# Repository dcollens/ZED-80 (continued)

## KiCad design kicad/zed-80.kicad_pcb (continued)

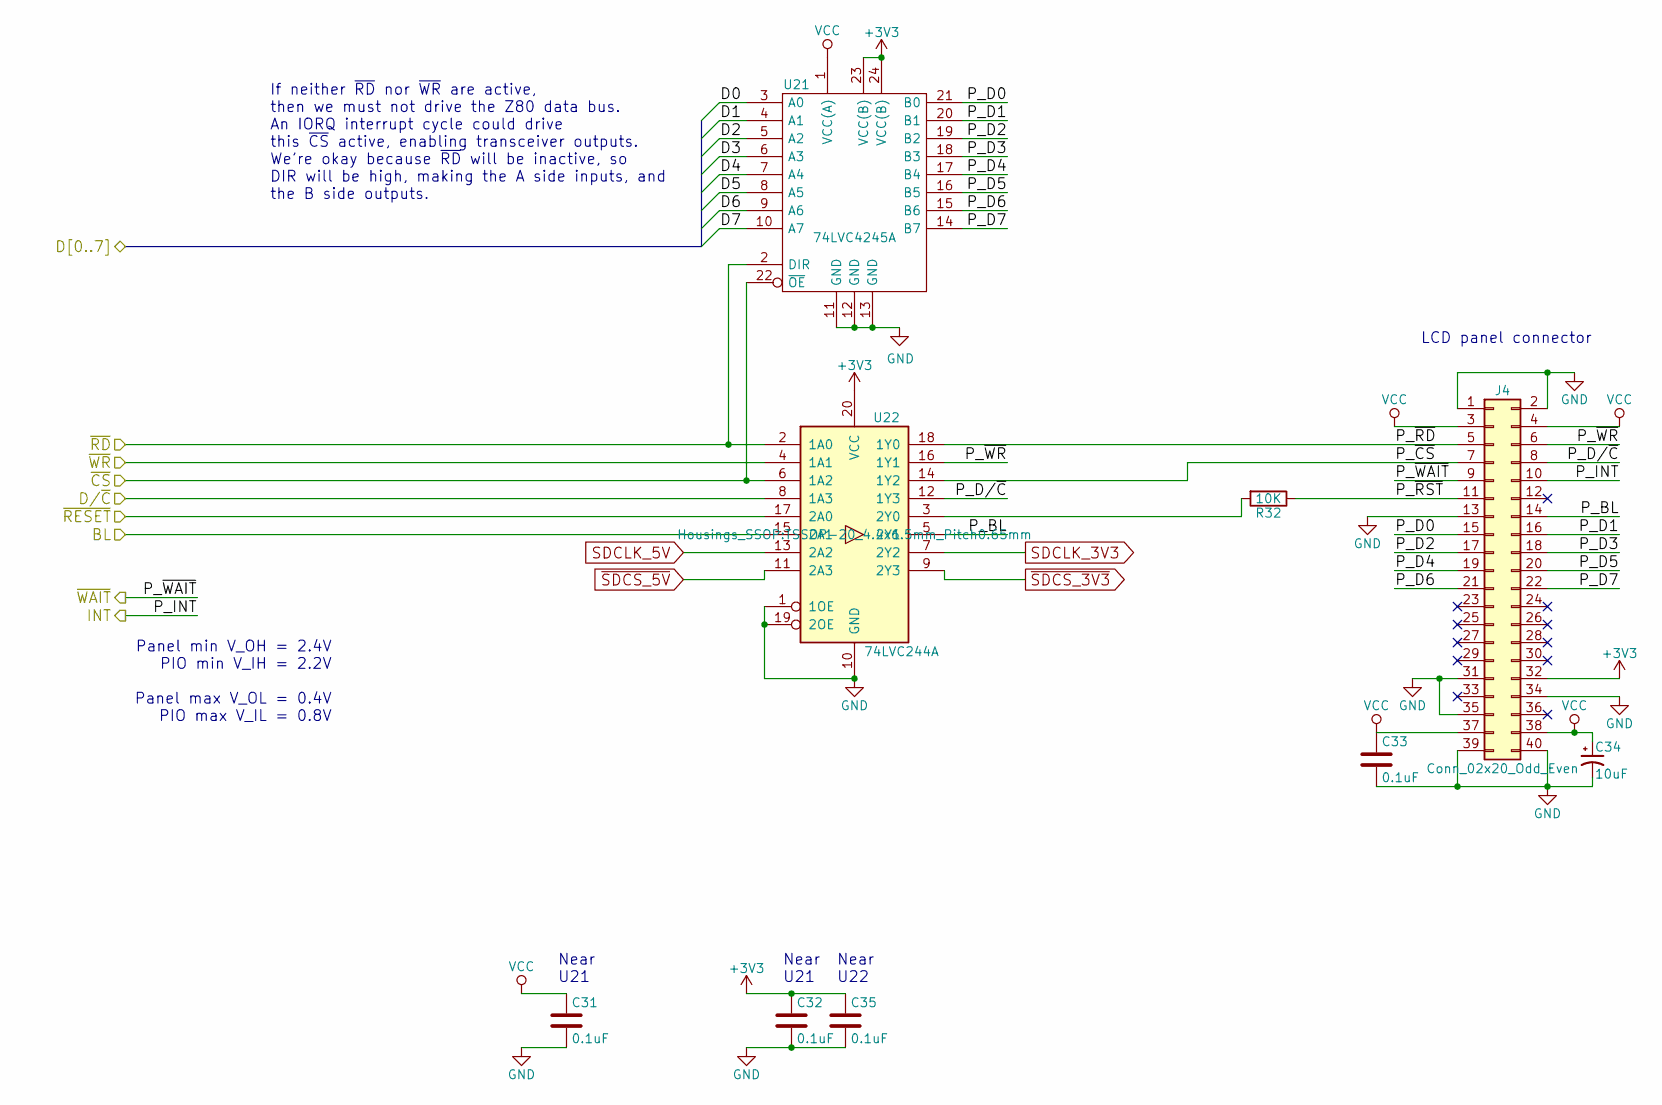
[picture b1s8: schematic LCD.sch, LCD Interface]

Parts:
C31, C32, C33, C35: 0.1uF; C_Disc_D4.3mm_W1.9mm_P5.00mm
C34: 10uF; CP_Radial_D5.0mm_P2.50mm
J4: Conn_02x20_Odd_Even; Pin_Header_Straight_2x20_Pitch2.54mm
R32: 10K; R_0805_HandSoldering
U21: 74LVC4245A; TSSOP-24_4.4x7.8mm_Pitch0.65mm
U22: 74LVC244A; TSSOP-20_4.4x6.5mm_Pitch0.65mm

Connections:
+3V3: C32.1, C35.1, J4.32, U21.23 (VCC(B)), U21.24 (VCC(B)), U22.20 (VCC); also elsewhere on the board
/A0: U22.8 (1A3); also elsewhere on the board
/D0: U21.3 (A0); also elsewhere on the board
/D1: U21.4 (A1); also elsewhere on the board
/D2: U21.5 (A2); also elsewhere on the board
/D3: U21.6 (A3); also elsewhere on the board
/D4: U21.7 (A4); also elsewhere on the board
/D5: U21.8 (A5); also elsewhere on the board
/D6: U21.9 (A6); also elsewhere on the board
/D7: U21.10 (A7); also elsewhere on the board
/LCD/BL: U22.15 (2A1); also elsewhere on the board
/LCD/INT: J4.10; also elsewhere on the board
/LCD/P_BL: J4.14, U22.5 (2Y1)
/LCD/P_D0: J4.15, U21.21 (B0)
/LCD/P_D1: J4.16, U21.20 (B1)
/LCD/P_D2: J4.17, U21.19 (B2)
/LCD/P_D3: J4.18, U21.18 (B3)
/LCD/P_D4: J4.19, U21.17 (B4)
/LCD/P_D5: J4.20, U21.16 (B5)
/LCD/P_D6: J4.21, U21.15 (B6)
/LCD/P_D7: J4.22, U21.14 (B7)
/LCD/P_D/~C: J4.8, U22.12 (1Y3)
/LCD/P_~CS: J4.7, U22.14 (1Y2)
/LCD/P_~RD: J4.5, U22.18 (1Y0)
/LCD/P_~RST: J4.11, R32.1
/LCD/P_~WR: J4.6, U22.16 (1Y1)
/PIO/PIOA7: J4.9; also elsewhere on the board
/~IORQ5: U21.22 (~OE), U22.6 (1A2); also elsewhere on the board
/~RD: U21.2 (DIR), U22.2 (1A0); also elsewhere on the board
/~RESET: U22.17 (2A0); also elsewhere on the board
/~WR: U22.4 (1A1); also elsewhere on the board
GND: C31.2, C32.2, C33.2, C34.2, C35.2, J4.1, J4.2, J4.13, J4.31, J4.34, J4.35, J4.39, J4.40, U21.11 (GND), U21.12 (GND), U21.13 (GND), U22.1 (1OE), U22.10 (GND), U22.19 (2OE); also elsewhere on the board
unnamed: R32.2, U22.3 (2Y0)
SDCLK_3V3: U22.7 (2Y2); also elsewhere on the board
SDCLK_5V: U22.13 (2A2); also elsewhere on the board
VCC: C31.1, C33.1, C34.1, J4.3, J4.4, J4.37, J4.38, U21.1 (VCC(A)); also elsewhere on the board
~SDCS_3V3: U22.9 (2Y3); also elsewhere on the board
~SDCS_5V: U22.11 (2A3); also elsewhere on the board

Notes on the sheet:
LCD panel connector
Near U21
Panel min V_OH = 2.4V PIO min V_IH = 2.2V Panel max V_OL = 0.4V PIO max V_IL = 0.8V
Near U22
If neither ~RD~ nor ~WR~ are active, then we must not drive the Z80 data bus. An IORQ interrupt cycle could drive this ~CS~ active, enabling transceiver outputs. We’re okay because ~RD~ will be inactive, so DIR will be high, making the A side inputs, and the B side outputs.

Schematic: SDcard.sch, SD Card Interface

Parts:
C36, C39, C40: 0.1uF; C_Disc_D4.3mm_W1.9mm_P5.00mm
J7: SD_Card; 101-00405
R33: 50K; R_0805_HandSoldering
R34, R35: 10K; R_0805_HandSoldering
U4: 74AHC32; DIP-14_W7.62mm
U25: 74HCT164; TSSOP-14_4.4x5mm_Pitch0.65mm
U26: 74AHC541; TSSOP-20_4.4x6.5mm_Pitch0.65mm
U27: 74LV165; TSSOP-16_4.4x5mm_Pitch0.65mm

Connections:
+3V3: C36.1, J7.4 (VDD), R33.2, U27.16 (VCC); also elsewhere on the board
/D0: U26.18 (Y0), U27.11 (D0); also elsewhere on the board
/D1: U26.17 (Y1), U27.12 (D1); also elsewhere on the board
/D2: U26.16 (Y2), U27.13 (D2); also elsewhere on the board
/D3: U26.15 (Y3), U27.14 (D3); also elsewhere on the board
/D4: U26.14 (Y4), U27.3 (D4); also elsewhere on the board
/D5: U26.13 (Y5), U27.4 (D5); also elsewhere on the board
/D6: U26.12 (Y6), U27.5 (D6); also elsewhere on the board
/D7: U26.11 (Y7), U27.6 (D7); also elsewhere on the board
/Joystick Ports/~SDCD: J7.10 (CARD_DETECT), R35.2; also elsewhere on the board
/Joystick Ports/~SDWP: J7.11 (WRITE_PROTECT), R34.2; also elsewhere on the board
/SDOCLK: U27.2 (CP); also elsewhere on the board
/~IORQ8: U4.10, U26.1 (G1); also elsewhere on the board
/~RD: U26.19 (G2); also elsewhere on the board
/~SDICLR: U25.9 (~CLR); also elsewhere on the board
/~WR: U4.9; also elsewhere on the board
GND: C36.2, C39.2, C40.2, J7.3 (VSS), J7.6 (VSS), J7.12 (SHELL1), J7.13 (SHELL2), U25.7 (GND), U26.10 (GND), U27.8 (GND), U27.10 (DS), U27.15 (~CE); also elsewhere on the board
unnamed: J7.2 (CMD), U27.9 (Q7)
unnamed: J7.7 (DAT0), R33.1, U25.1 (A)
unnamed: U25.3 (Qa), U26.2 (A0)
unnamed: U25.4 (Qb), U26.3 (A1)
unnamed: U25.5 (Qc), U26.4 (A2)
unnamed: U25.6 (Qd), U26.5 (A3)
unnamed: U25.10 (Qe), U26.6 (A4)
unnamed: U25.11 (Qf), U26.7 (A5)
unnamed: U25.12 (Qg), U26.8 (A6)
unnamed: U25.13 (Qh), U26.9 (A7)
unnamed: U4.8, U27.1 (~PL)
SDCLK_3V3: J7.5 (CLK); also elsewhere on the board
SDCLK_5V: U25.8 (CLK); also elsewhere on the board
VCC: C39.1, C40.1, R34.1, R35.1, U25.2 (B), U25.14 (VCC), U26.20 (VCC); also elsewhere on the board
~SDCS_3V3: J7.1 (CD/DAT3); also elsewhere on the board

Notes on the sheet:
Near U27
See LCD page for level conversion.
Near U25
Near U26

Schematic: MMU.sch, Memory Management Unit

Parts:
C37: 0.1uF; C_Disc_D4.3mm_W1.9mm_P5.00mm
D2, D3, D4, D5: D_ALT; D_SOT-23_ANK
U2: 74AHC14; DIP-14_W7.62mm
U4: 74AHC32; DIP-14_W7.62mm
U24: 74HC670; SOIC-16_3.9x9.9mm_Pitch1.27mm

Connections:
/A0: U24.14 (Wa); also elsewhere on the board
/A1: U24.13 (Wb); also elsewhere on the board
/A14: U24.5 (Ra); also elsewhere on the board
/A15: U24.4 (Rb); also elsewhere on the board
/D0: U24.15 (D1); also elsewhere on the board
/D1: U24.1 (D2); also elsewhere on the board
/D2: U24.2 (D3); also elsewhere on the board
/D3: U24.3 (D4); also elsewhere on the board
/MMUEN: D2.1 (K), D3.1 (K), D4.1 (K), D5.1 (K), U2.5; also elsewhere on the board
/PA14: D5.2 (A), U24.10 (Q1); also elsewhere on the board
/PA15: D4.2 (A), U24.9 (Q2); also elsewhere on the board
/PA16: D3.2 (A), U24.7 (Q3); also elsewhere on the board
/PA17: D2.2 (A), U24.6 (Q4); also elsewhere on the board
/~IORQ6: U4.1; also elsewhere on the board
/~WR: U4.2; also elsewhere on the board
GND: C37.2, U24.8 (GND); also elsewhere on the board
unnamed: U2.6, U24.11 (~Er)
unnamed: U4.3, U24.12 (~Ew)
VCC: C37.1, U24.16 (VCC); also elsewhere on the board

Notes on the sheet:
Near U24

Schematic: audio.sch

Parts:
C42: 0.1uF; C_Disc_D4.3mm_W1.9mm_P5.00mm
C44: 47uF; CP_Radial_D6.3mm_P2.50mm
J8: SJ1-3523N
J9: Conn_02x09_Odd_Even; Pin_Header_Straight_2x09_Pitch2.54mm
R36: 100R; R_0805_HandSoldering
R37, R38, R39: 1K; R_0805_HandSoldering
U29: AY-3-8910; DIP-40_W15.24mm_Socket

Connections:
/Audio/D0: U29.37 (DA0); also elsewhere on the board
/Audio/D1: U29.36 (DA1); also elsewhere on the board
/Audio/D2: U29.35 (DA2); also elsewhere on the board
/Audio/D3: U29.34 (DA3); also elsewhere on the board
/Audio/D4: U29.33 (DA4); also elsewhere on the board
/Audio/D5: U29.32 (DA5); also elsewhere on the board
/Audio/D6: U29.31 (DA6); also elsewhere on the board
/Audio/D7: U29.30 (DA7); also elsewhere on the board
/BC1: U29.29 (BC1); also elsewhere on the board
/BDIR: U29.27 (BDIR); also elsewhere on the board
/CLK2M: U29.22 (CLK); also elsewhere on the board
/~RESET: U29.23 (~RESET); also elsewhere on the board
GND: C42.2, J8.S, J9.18, R36.2, U29.1 (GND), U29.24 (~A9); also elsewhere on the board
unnamed: C44.1, R36.1, R37.1, R38.1, R39.1
unnamed: C44.2, J8.R, J8.T
unnamed: J9.2, U29.6 (IOB7)
unnamed: J9.3, U29.21 (IOA0)
unnamed: J9.4, U29.7 (IOB6)
unnamed: J9.5, U29.20 (IOA1)
unnamed: J9.6, U29.8 (IOB5)
unnamed: J9.7, U29.19 (IOA2)
unnamed: J9.8, U29.9 (IOB4)
unnamed: J9.9, U29.18 (IOA3)
unnamed: J9.10, U29.10 (IOB3)
unnamed: J9.11, U29.17 (IOA4)
unnamed: J9.12, U29.11 (IOB2)
unnamed: J9.13, U29.16 (IOA5)
unnamed: J9.14, U29.12 (IOB1)
unnamed: J9.15, U29.15 (IOA6)
unnamed: J9.16, U29.13 (IOB0)
unnamed: J9.17, U29.14 (IOA7)
unnamed: R37.2, U29.4 (CH_A)
unnamed: R38.2, U29.3 (CH_B)
unnamed: R39.2, U29.38 (CH_C)
VCC: C42.1, J9.1, U29.25 (A8), U29.28 (BC2), U29.40 (VCC); also elsewhere on the board

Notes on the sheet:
BDIR BC1 Meaning 0 0 Idle 0 1 Read data 1 0 Write data 1 1 Write address
Near U29

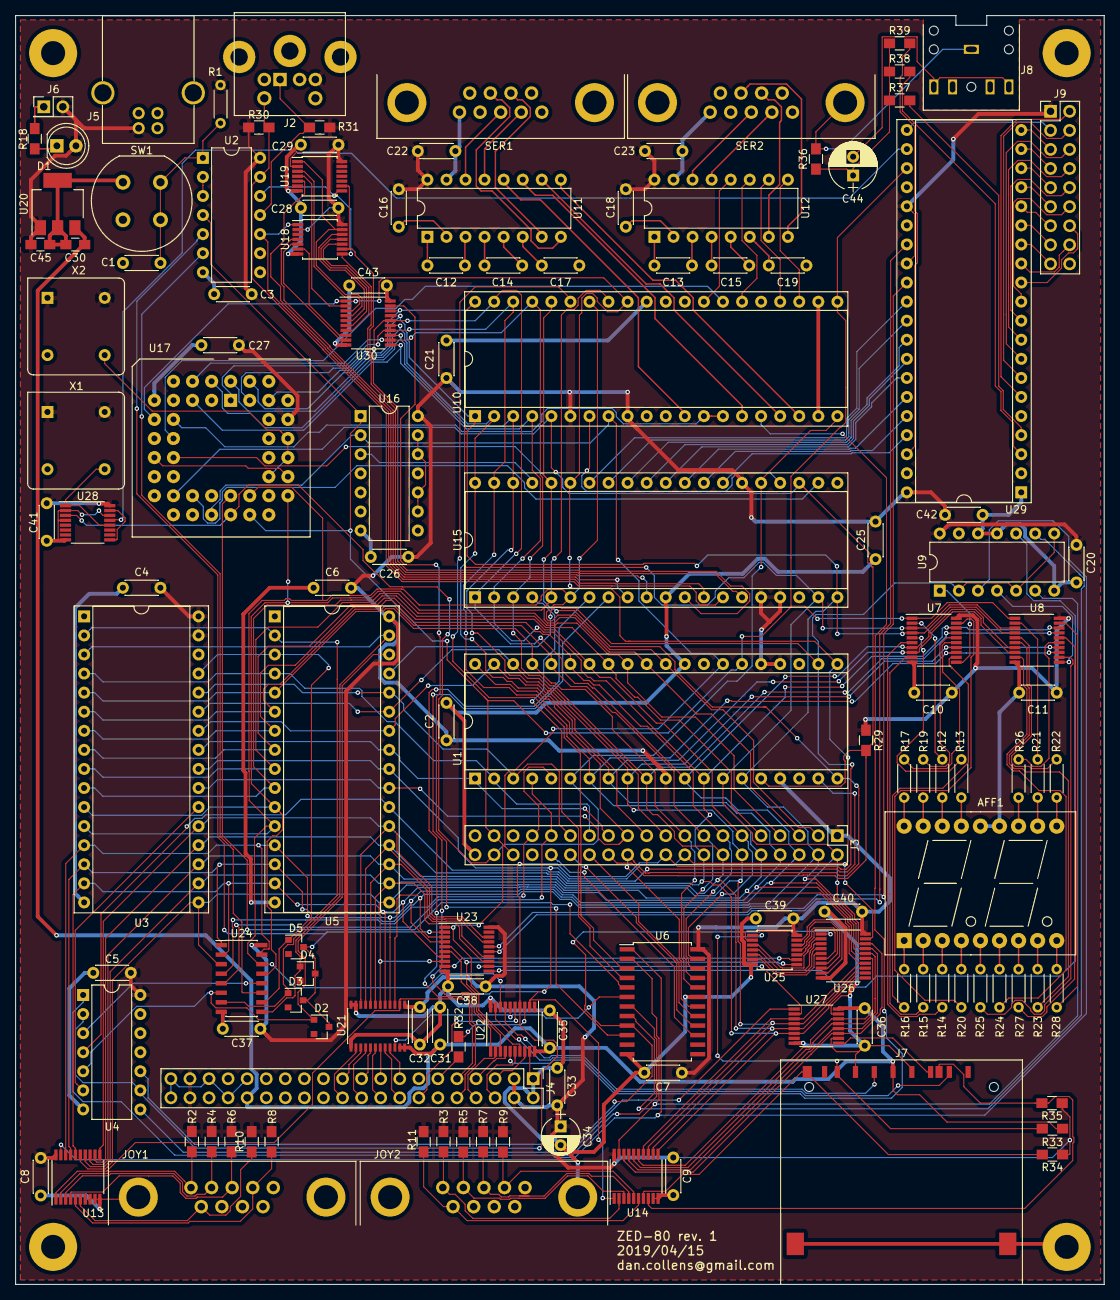
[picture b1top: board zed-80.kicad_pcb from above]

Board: 2 copper layers, 145.0 x 169.0 mm, 138 parts (0 on the bottom side), 225 nets.

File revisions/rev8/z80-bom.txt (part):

Source:	/Users/dcollens/Documents/depot/main/z80/z80.sch
Date:	Tuesday, June 05, 2018 'amt' 10:21:38 am
Tool:	Eeschema 4.0.7
Component Count:	93
Ref	Value	Part	Footprint	Description	Vendor
AFF1	LTD-6940HR	headquarters:LTD-6940HR	z80_footprints:LTD-6940HR	DISPLAY 7 SEGMENTS common K	
C1	0.1uF	device:C	Capacitors_THT:C_Disc_D4.3mm_W1.9mm_P5.00mm	Unpolarized capacitor	
C2	0.1uF	device:C	Capacitors_THT:C_Disc_D4.3mm_W1.9mm_P5.00mm	Unpolarized capacitor	
C3	0.1uF	device:C	Capacitors_THT:C_Disc_D4.3mm_W1.9mm_P5.00mm	Unpolarized capacitor	
C4	0.1uF	device:C	Capacitors_THT:C_Disc_D4.3mm_W1.9mm_P5.00mm	Unpolarized capacitor	
C5	0.1uF	device:C	Capacitors_THT:C_Disc_D4.3mm_W1.9mm_P5.00mm	Unpolarized capacitor	
C6	0.1uF	device:C	Capacitors_THT:C_Disc_D4.3mm_W1.9mm_P5.00mm	Unpolarized capacitor	
C7	0.1uF	device:C	Capacitors_THT:C_Disc_D4.3mm_W1.9mm_P5.00mm	Unpolarized capacitor	
C8	0.1uF	device:C	Capacitors_THT:C_Disc_D4.3mm_W1.9mm_P5.00mm	Unpolarized capacitor	
C9	0.1uF	device:C	Capacitors_THT:C_Disc_D4.3mm_W1.9mm_P5.00mm	Unpolarized capacitor	
C10	0.1uF	device:C	Capacitors_THT:C_Disc_D4.3mm_W1.9mm_P5.00mm	Unpolarized capacitor	
C11	0.1uF	device:C	Capacitors_THT:C_Disc_D4.3mm_W1.9mm_P5.00mm	Unpolarized capacitor	
C12	0.1uF	device:C	Capacitors_THT:C_Disc_D4.3mm_W1.9mm_P5.00mm	Unpolarized capacitor	
C13	0.1uF	device:C	Capacitors_THT:C_Disc_D4.3mm_W1.9mm_P5.00mm	Unpolarized capacitor	
C14	0.1uF	device:C	Capacitors_THT:C_Disc_D4.3mm_W1.9mm_P5.00mm	Unpolarized capacitor	
C15	0.1uF	device:C	Capacitors_THT:C_Disc_D4.3mm_W1.9mm_P5.00mm	Unpolarized capacitor	
C16	0.1uF	device:C	Capacitors_THT:C_Disc_D4.3mm_W1.9mm_P5.00mm	Unpolarized capacitor	
C17	0.1uF	device:C	Capacitors_THT:C_Disc_D4.3mm_W1.9mm_P5.00mm	Unpolarized capacitor	
C18	0.1uF	device:C	Capacitors_THT:C_Disc_D4.3mm_W1.9mm_P5.00mm	Unpolarized capacitor	
C19	0.1uF	device:C	Capacitors_THT:C_Disc_D4.3mm_W1.9mm_P5.00mm	Unpolarized capacitor	
C20	0.1uF	device:C	Capacitors_THT:C_Disc_D4.3mm_W1.9mm_P5.00mm	Unpolarized capacitor	
C21	0.1uF	device:C	Capacitors_THT:C_Disc_D4.3mm_W1.9mm_P5.00mm	Unpolarized capacitor	
C22	0.1uF	device:C	Capacitors_THT:C_Disc_D4.3mm_W1.9mm_P5.00mm	Unpolarized capacitor	
C23	0.1uF	device:C	Capacitors_THT:C_Disc_D4.3mm_W1.9mm_P5.00mm	Unpolarized capacitor	
C24	10uF	device:CP1_Small	Capacitors_THT:C_Disc_D4.3mm_W1.9mm_P5.00mm	Polarised capacitor	
C25	0.1uF	device:C	Capacitors_THT:C_Disc_D4.3mm_W1.9mm_P5.00mm	Unpolarized capacitor	
C26	0.1uF	device:C	Capacitors_THT:C_Disc_D4.3mm_W1.9mm_P5.00mm	Unpolarized capacitor	
C27	0.1uF	device:C	Capacitors_THT:C_Disc_D4.3mm_W1.9mm_P5.00mm	Unpolarized capacitor	
C28	0.1uF	device:C	Capacitors_THT:C_Disc_D4.3mm_W1.9mm_P5.00mm	Unpolarized capacitor	
C29	0.1uF	device:C	Capacitors_THT:C_Disc_D4.3mm_W1.9mm_P5.00mm	Unpolarized capacitor	
D1	Green	device:LED_Small_ALT	LEDs:LED_D5.0mm	LED, small symbol, alternativ symbol	
J1	Conn_02x08_Odd_Even	conn:Conn_02x08_Odd_Even	Pin_Headers:Pin_Header_Straight_2x08_Pitch2.54mm	Generic connector, double row, 02x08, odd/even pin numbering scheme (row 1 odd numbers, row 2 even numbers)	
J2	KMDGX-6S-BS	headquarters:KMDGX-6S-BS	z80_footprints:KMDGX-6S-BS	6-pin Mini-DIN connector	
J3	Conn_02x20_Odd_Even	conn:Conn_02x20_Odd_Even	Pin_Headers:Pin_Header_Straight_2x20_Pitch2.54mm	Generic connector, double row, 02x20, odd/even pin numbering scheme (row 1 odd numbers, row 2 even numbers)	
J5	USB_B	conn:USB_B	z80_footprints:USB_B_E8144-B02022-L	USB Type B connector	
J6	PWR	conn:Conn_01x02	Pin_Headers:Pin_Header_Straight_2x01_Pitch2.54mm	Generic connector, single row, 01x02	
JOY1	DB9-M	conn:DB9_Male_MountingHoles	z80_footprints:L717SDE09P1ACH	9-pin male D-SUB connector, Mounting Hole	
JOY2	DB9-M	conn:DB9_Male_MountingHoles	z80_footprints:L717SDE09P1ACH	9-pin male D-SUB connector, Mounting Hole	
R1	1M	device:R	Resistors_THT:R_Axial_DIN0204_L3.6mm_D1.6mm_P5.08mm_Horizontal	Resistor	
R2	10K	device:R	Resistors_THT:R_Axial_DIN0204_L3.6mm_D1.6mm_P5.08mm_Horizontal	Resistor	
R3	10K	device:R	Resistors_THT:R_Axial_DIN0204_L3.6mm_D1.6mm_P5.08mm_Horizontal	Resistor	
R4	10K	device:R	Resistors_THT:R_Axial_DIN0204_L3.6mm_D1.6mm_P5.08mm_Horizontal	Resistor	
R5	10K	device:R	Resistors_THT:R_Axial_DIN0204_L3.6mm_D1.6mm_P5.08mm_Horizontal	Resistor	
R6	10K	device:R	Resistors_THT:R_Axial_DIN0204_L3.6mm_D1.6mm_P5.08mm_Horizontal	Resistor	
R7	10K	device:R	Resistors_THT:R_Axial_DIN0204_L3.6mm_D1.6mm_P5.08mm_Horizontal	Resistor	
R8	10K	device:R	Resistors_THT:R_Axial_DIN0204_L3.6mm_D1.6mm_P5.08mm_Horizontal	Resistor	
R9	10K	device:R	Resistors_THT:R_Axial_DIN0204_L3.6mm_D1.6mm_P5.08mm_Horizontal	Resistor	
R10	10K	device:R	Resistors_THT:R_Axial_DIN0204_L3.6mm_D1.6mm_P5.08mm_Horizontal	Resistor	
R11	10K	device:R	Resistors_THT:R_Axial_DIN0204_L3.6mm_D1.6mm_P5.08mm_Horizontal	Resistor	
R12	220R	device:R	Resistors_THT:R_Axial_DIN0204_L3.6mm_D1.6mm_P5.08mm_Horizontal	Resistor	
R13	220R	device:R	Resistors_THT:R_Axial_DIN0204_L3.6mm_D1.6mm_P5.08mm_Horizontal	Resistor	
R14	220R	device:R	Resistors_THT:R_Axial_DIN0204_L3.6mm_D1.6mm_P5.08mm_Horizontal	Resistor	
R15	220R	device:R	Resistors_THT:R_Axial_DIN0204_L3.6mm_D1.6mm_P5.08mm_Horizontal	Resistor	
R16	220R	device:R	Resistors_THT:R_Axial_DIN0204_L3.6mm_D1.6mm_P5.08mm_Horizontal	Resistor	
R17	220R	device:R	Resistors_THT:R_Axial_DIN0204_L3.6mm_D1.6mm_P5.08mm_Horizontal	Resistor	
R18	10K	device:R	Resistors_THT:R_Axial_DIN0204_L3.6mm_D1.6mm_P5.08mm_Horizontal	Resistor	
R19	220R	device:R	Resistors_THT:R_Axial_DIN0204_L3.6mm_D1.6mm_P5.08mm_Horizontal	Resistor	
R20	220R	device:R	Resistors_THT:R_Axial_DIN0204_L3.6mm_D1.6mm_P5.08mm_Horizontal	Resistor	
R21	220R	device:R	Resistors_THT:R_Axial_DIN0204_L3.6mm_D1.6mm_P5.08mm_Horizontal	Resistor	
R22	220R	device:R	Resistors_THT:R_Axial_DIN0204_L3.6mm_D1.6mm_P5.08mm_Horizontal	Resistor	
R23	220R	device:R	Resistors_THT:R_Axial_DIN0204_L3.6mm_D1.6mm_P5.08mm_Horizontal	Resistor	
R24	220R	device:R	Resistors_THT:R_Axial_DIN0204_L3.6mm_D1.6mm_P5.08mm_Horizontal	Resistor	
R25	220R	device:R	Resistors_THT:R_Axial_DIN0204_L3.6mm_D1.6mm_P5.08mm_Horizontal	Resistor	
R26	220R	device:R	Resistors_THT:R_Axial_DIN0204_L3.6mm_D1.6mm_P5.08mm_Horizontal	Resistor	
R27	220R	device:R	Resistors_THT:R_Axial_DIN0204_L3.6mm_D1.6mm_P5.08mm_Horizontal	Resistor	
R28	220R	device:R	Resistors_THT:R_Axial_DIN0204_L3.6mm_D1.6mm_P5.08mm_Horizontal	Resistor	
R29	10K	device:R	Resistors_THT:R_Axial_DIN0204_L3.6mm_D1.6mm_P5.08mm_Horizontal	Resistor	
R30	10K	device:R	Resistors_THT:R_Axial_DIN0204_L3.6mm_D1.6mm_P5.08mm_Horizontal	Resistor	
R31	10K	device:R	Resistors_THT:R_Axial_DIN0204_L3.6mm_D1.6mm_P5.08mm_Horizontal	Resistor	
SER1	DB9-M	conn:DB9_Male_MountingHoles	z80_footprints:L717SDE09P1ACH	9-pin male D-SUB connector, Mounting Hole	
SER2	DB9-M	conn:DB9_Male_MountingHoles	z80_footprints:L717SDE09P1ACH	9-pin male D-SUB connector, Mounting Hole	
SW1	KS01Q	switches:SW_Push	z80_footprints:KS-01Q-02	Push button switch, generic, two pins	
U1	Z80CPU	Zilog:Z80CPU	Housings_DIP:DIP-40_W15.24mm_Socket_LongPads	8-bit General Purpose Microprocessor, DIP-40	
U2	74AHC14	74xx:74HC14	Housings_DIP:DIP-14_W7.62mm_LongPads	Hex Inverseur	
U3	SST39SF010	memory:SST39SF010	Housings_DIP:DIP-32_W15.24mm_Socket_LongPads	Silicon Storage Technology (SSF) 128k x 8 Flash ROM	
U4	74AHC32	74xx:74LS32	Housings_DIP:DIP-14_W7.62mm_LongPads	Quad Or 2 inputs	
U5	AS6C1008-55PCN	headquarters:AS6C1008-55SIN	Housings_DIP:DIP-32_W15.24mm_Socket_LongPads	1Mbit 128Kx8 Static RAM	
U6	74AHC138	74xx:74LS138	Housings_DIP:DIP-16_W7.62mm_LongPads	Decoder 3 to 8 (active low outputs)	
U7	74AC574	74xx:74LS574	Housings_DIP:DIP-20_W7.62mm_LongPads	8 bits Register, 3 state Out	
U8	74AC574	74xx:74LS574	Housings_DIP:DIP-20_W7.62mm_LongPads	8 bits Register, 3 state Out	
U9	74AHC02	74xx:74HC02	Housings_DIP:DIP-14_W7.62mm_LongPads	Quad Nor2	
U10	Z84C40	headquarters:Z84C40	Housings_DIP:DIP-40_W15.24mm_Socket_LongPads	Z80 Serial I/O	
U11	SP232E	interface:MAX232	Housings_DIP:DIP-16_W7.62mm_LongPads	Dual RS232 driver/receiver, 5V supply, 120kb/s, 0C-70C	
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
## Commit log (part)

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2017-10-23 Initial checkin of z80 prototype project.
2017-11-05 Latest rev of z80 schematic.
2018-04-11 Assign footprints to schematic, drawing custom connector, socket, and switch footprints as needed.
2018-05-31 Initial prototype PCB build.
2018-06-12 Clean up and archive everything for revision 8.
2018-06-13 Update schematic & layout to fix reversed keyboard port pinout. Update test programs for PCB. Write test code for joystick port.
2018-06-16 Add support for SIO chip; write test program that writes messages out serial port.
2018-06-19 Serial I/O test is now an echo-back test.
2018-07-03 Beginnings of ROM debug monitor (can read from I/O ports, and reset the machine).
2018-07-11 Get ROM monitor packet I/O working. Can now load and run programs over serial port.
2018-07-16 Docs for LCD module.
2018-10-13 Port NASCOM BASIC to the prototype Z80 board. Get Super Star Trek BASIC program running.
2018-10-26 Move Kicad files into a subfolder.
2018-11-06 First cut at ZED-80 emulator. Only output so far is to terminal.
2019-01-17 Working on SD card interface, cleaning up.
2019-03-22 Hook up SD card slot's write protect and card detect lines.
2019-04-02 Clean up old backup files.
2019-04-02 Rename Kicad project from "z80" to "zed-80".
2019-04-05 Revive joystick-based test program.
2019-04-11 Assign footprints.
2019-04-11 Add SD card footprint.
2019-04-16 Finalize layout of ZED-80 rev. 1
2019-04-28 Hide footprint value on schematic.
2019-04-29 Move old Z80 software to z80-prototype folder, as it depends on the memory map of the prototype board. Create new zed-80 folder for software for the real ZED-80 board, and start copying/updating some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
2019-04-30 Add system register and modify MMU to match recent hardware.
2019-04-30 Add LCD test program. So far it blinks the LCD backlight.
2019-04-30 Start GUI.
2019-04-30 Add docs for getting zasm.
2019-04-30 Add GUI command to start/stop emulator.
2019-05-01 Move emulator project to Objective C++.
2019-05-01 Pass UI delegate down emulator.
2019-05-01 Add Xcode schemes.
2019-05-01 Switch to the HeadCode team so that LK and I can both develop without having to manually switch back and forth between our respective personal teams.
2019-05-01 Check in shared schemes created by Xcode
2019-05-16 Check in RA8876 sample reference code (incl. preprocessed version).
2019-05-16 Enable/disable menu items appropriately.
2019-05-17 Flesh out LCD panel support in the emulator. Fix bug in MMU which discarded offset within page on all accesses when MMU enabled. Allow loading of arbitrary regions of ROM and RAM from multiple files 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
2019-05-17 Detect user to determine ROM path.
2019-05-17 Don't check in rom/ram/lst files.
2019-05-17 Flip LCD upside down.
2019-05-18 Generate PS/2 scan codes from Mac key codes.
2019-05-22 Emulate the CTC, including timer interrupts.
2019-05-22 Simulate PIO chip (not yet connected to any downstream devices).
2019-05-23 Emulate AY-3-8910, including audio output to host. Switch to rom_ram_test.rom so you can hear the boot sound.
2019-05-24 Check that ROM/BIN is up to date.
2019-05-24 Clean up the keycode map for the emulator. Implement a polling-mode keyboard driver for the ZED-80, and attach it to the LCD so you can type (unmodified) keys and see them echo back on the LCD. Still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
2019-05-24 Remove command-line emulator target since it no longer makes any sense.
2019-05-24 Cleanups.
2019-05-25 Add gets() routine.
2019-05-25 Only call iommu if doing read or write.
    The previous code was calling the iommu if the IORQ line
    was asserted, but (apparently!) the address pins are not
    valid at this time, and the iommu was dispatching to
    a bogus device. (The symptom was a warning for IO access
    to the unimplemented SD card $80.) Added a check to
    read or write before dispatching to iommu.
2019-05-25 Add pin history for debugging.
2019-05-25 Use a different ROM for the emulator.
2019-05-25 Add decimal and hex printing routines.
2019-05-25 Can push immediates.
2019-05-25 Forth: enter and exit work.
2019-05-25 Rename gets() to lcd_gets() for now to make it clear that it operates on the console and not serial port. Maybe this should be called kbd_gets, or maybe con_gets (for "console") since it uses the loc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
2019-05-25 Fix Collins' busted code.
2019-05-25 Add Command-R Reload menu item to emulator.
2019-05-25 Convert dot and imm to native.
2019-05-25 Implement cooked input with SHIFT key modifier support.
2019-05-25 Implement >cfa.
2019-05-25 Implement modifier keys in the emulator.
2019-05-25 Can push new numbers onto the Forth stack.
2019-05-25 Implement backspace in lcd_gets.
2019-05-25 Add literal to parsing.
2019-05-25 Proper parsing of words.
2019-05-25 Enforce buffer size limit in lcd_gets.
2019-05-25 Actually fill buffer in gets().
2019-05-26 Tidy up the pin history code; use it to find the last few port 0x2x IORQs.
2019-05-26 Put interpret word in infinite loop.
2019-05-26 Add flags byte to words.
2019-05-26 Emulate cursor (with blink!)
2019-05-26 Add colon and semicolon.
2019-05-26 Convert tick to a compile-time version.
2019-05-26 Add line word.
2019-05-26 Add drop, swap, @, and !.
2019-05-26 Add I/O instructions.
2019-05-26 Convert 'words' to Forth.
2019-05-26 Add multiply and divide.
2019-05-26 Add else, <, and u.
2019-05-28 Implement BTE operations in emulator to support scrolling.
2019-06-01 Begin factoring shared routines out into a library (see 'lib' folder). Lots more to do. Will see how this works out, and then re-assess.
2019-06-01 Add missing dependencies.
2019-06-03 Skeletal implementation of SIO emulation. Re-enable SIO code in emulator's ROM monitor (display ROM monitor startup message).
2019-06-03 Beginnings of SD-card test program: display card presence and write-protect status.
2019-06-06 Add beep to forth.
2019-06-06 Add and and or to Forth.
2019-06-06 Add game to Forth.
2019-06-06 Can play song.
2019-06-09 Move joystick ops to pure Forth.
2019-06-09 Limit game sprite to screen.
2019-06-09 Add rect and rectf to Forth.
2019-06-09 Start of YM editor.
2019-06-09 Use keyboard for ym editor instead of joystick.
2019-06-09 Better Forth parsing; split out init Forth code.
2019-06-13 Get serious about real-time emulation, so that the rate at which we fill the audio buffers closely matches the rate at which audio is consumed by the audio output driver. Delay the start of audio pla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
    The beep sound now plays correctly.
2019-06-13 Split lcd_test into 3 programs: - forth - lcd_test - song and factor out shared code into the library.
2019-06-13 Increase length of Axel F song to close to the maximum that will fit in RAM.
2019-06-22 Add instructions for minicom without a profile.
2019-06-29 Successfully initialize (to the "ready" state) both v1 and v2 type cards (tested on 3 generations of card).
2019-06-29 Send CMD58 to determine byte vs. block addressing mode.
2019-08-19 Add script to compile and run forth.
2019-10-02 SD card test program can read and dump a sector.
2019-10-03 BASIC > FORTH. Tested on emulator only.
2019-10-13 Add more commented-out lines for other code images (e.g. BASIC)
2019-10-13 Invoke regular ROM monitor from emulator by default so you can try the new "B" command to launch BASIC. (Auto-execing emulator just commented out.) Suppress infinite audio buffer underflow messages w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
2019-10-13 Add a "forth_low.asm" that is setup to load at address 0. Include Forth runtime in ROM image. Add "F" command to launch Forth runtime from ROM monitor.
2019-12-08 Rough first pass at implementing a CBIOS.
2019-12-08 Fix command to read a sector.
2019-12-08 Write sectors using safe ASCII.
2019-12-08 First cut at SD card emulation.
2019-12-08 More progress on CP/M port; still busted but LK wants to have a look.
2019-12-08 Add CP/M programs.
2019-12-08 Fix safe write.
2019-12-08 Nicer MMU logging.
2019-12-14 Fix bug in CBIOS where CONST could return true but CONIN would subsequently block. This would hang the CP/M output routine because it calls CONST/CONIN to check for CTRL-C during output.
2019-12-14 Implement SD card writing. Can't test on real hardware at the moment becauze my ZED-80 is hanging.
2019-12-15 Add WordStar 3.0.
2019-12-16 Implement CBIOS disk write routine.
2019-12-16 Don't truncate sdcard on sector write.
2019-12-16 Start VT100 emulation, untested.
2019-12-16 Centralize constants related to CP/M layout in cbios.inc Enlarge CBIOS by 512 bytes, from 2.5K to 3K.
2019-12-16 Handle VT100 H (positioning) command.
2019-12-16 Handle VT100 K (clear to eol) command.
2019-12-16 Move VT100 data to RAM.
2019-12-17 Minor cleanups.
2019-12-22 Add 'flashrom' make target to flash the ROM.
2019-12-24 Add test programs to study power anomaly.
2020-01-01 Get CP/M booting on the real hardware. Add a user 3 with the transient CP/M commands.
2020-01-01 Add instructions for using ROM burner.
2020-01-02 Hello world CP/M program, written in C. Slightly brittle (i.e. main has to be the first symbol in the file, and there's no real C library yet, no stack, no data segment, no heap, etc.)
2020-02-05 More details for Mark.
2020-02-06 New ROM monitor for Z80 prototype board that includes the BASIC interpreter.
2020-02-14 Latest ROM monitor build.
2020-03-14 Split keyboard driver into polling-mode and interrupt-mode variants. Use interrupt-driven keyboard driver for ROM monitor and kbd_test program, but leave BASIC, Forth, and CP/M using polling-mode for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
2020-03-14 Switch BASIC, Forth, and CP/M over to interrupt-driven keyboard driver.
2020-03-16 First attempt at a proper makefile using SDCC to build a CP/M app.
2020-03-28 Ignore SDCC build products.
2020-03-29 Move ZED-80 CP/M C library down into src/cpm/lib. Implement command-line parsing (argc, argv) for ZED-80 CP/M C library. Implement strdup (was missing from SDCC's C library). Update hello.c to dump c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
2020-03-29 Clean up FCB library routines.
2020-03-30 Implement some FILE* stdio routines for CP/M.
2020-03-30 Implement ymplay tool to play decompressed YM audio files. Does everything except actually play the sound data through the audio chip.
2020-04-14 Compile 'pkt' with C++11 so that it can build on older systems.
2020-04-19 Share Sysreg address between CBIOS and CP/M apps ($FFFE), and fill it in from the ROM monitor's Sysreg value when booting CP/M.
2020-10-25 Emulator: update for XCode 12.1
2020-10-25 CBIOS: add SETCTCISR entry point to set CTC ISRs ymplay: set 50Hz CTC timer tick and use it to sync playback
2020-10-26 CPM/SDCC: update to SDCC 4.0.0 which includes a strdup() implementation in its C library, so drop ours. CBIOS: add a SNDWRITE entry point to write data to the sound chip Rework the assembly code for 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
2020-11-12 YMPLAY: full ISR-driven playback with ring buffer
2020-11-12 Clean out some old SDCC testing code.
2020-11-13 Optimize sound chip writing code.
2020-11-13 YMPLAY: display elapsed time and progress of playback as a percentage
2020-11-19 CBIOS: properly implement cold boot entry point; only show welcome message on cold boots; preserve USER setting across warm boots ROM: invoke CBIOS cold boot entry point when user picks CP/M from the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
2020-11-19 C-library: provide access to all CP/M console I/O entry points, including "direct" I/O. YMPLAY: use direct console I/O to respond to ESC and 'q' to quit playback
2020-11-19 C library: add fseek & ftell YMPLAY: Ctrl-A to jump back to start of song
2020-11-20 C-library: add calls to search directory for files matching a pattern
2020-11-22 YMPLAY: play multiple tracks, and switch between them
2020-12-06 CHIP8: first cut at CHIP-8 emulator with passing opcode test Still need sound, keyboard, and proper display
2020-12-13 Add CONIOTST program to write chars to the display intensively.
2020-12-13 CONIOTST: add inter-character delay argument
2020-12-16 Emulator: draw glyphs directly into back buffer by copying them from a master font stencil image to speed up character display. Use C++17
2020-12-16 CHIP8: fix a bug in keyboard input opcodes; only poll keyboard input once per tick (to speed up emulation)
2020-12-16 CHIP8: check keyboard before redrawing screen
2020-12-17 Clean up Makefile.
2021-01-09 CHIP8: fix bug where CP/M would eat a single input character (buffered in BDOS) because we were using buffered/cooked output and it was looking for a control character in the input stream to pause th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
2021-01-24 CHIP8: draw pixels as white squares
2021-01-24 CHIP8: simplify code to use array of bool for keyboard state
